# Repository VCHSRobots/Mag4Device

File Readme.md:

# Mag4 Project -- 4 Way Interface for SRX-MAG Encoders

## Background

The SRX Mag Encoder developed by Cross the Road Electronics (CTRE) has
been a mainstay for FRC Robots for many years.  It provides the ability
to read the angular postion of a shaft and provides two signals: a PWM
signal for abolute angle measurements and a quadrature signal for relative
measurements.  The electrical interface to the device is a socket for
small 10-pin ribbon cable that carries power and signals.  This ribbon
cable is usually connected to a Talon SRX motor controller that has a
mating socket.  Once connected to the Talon, the encoded information can
be read at the RoboRio by way of the CAN bus.  However, CTRE makes other
compatable accessories for this 10-pin cable so that the signals and be
broken out for other interfaces. 

As of 2023, an SRX Mag Encoder costs about $40.00.

Around 2018, CTRE and Vex Robots introduced the Falon Motor which has
a motor control and encoder built in.  That is, a Falcon does not need a Talon.
Without Talons, a SRX Mag Encoder does not have a natural interface device.
To alevate this problem CTRE also introduced a "CANCoder" which is an upgrade
to the SRX Mag Encoder.  The CANCoder has the same features as the SRX Mag
Encoder, except that the 10-pin socket has been replaced by CAN wiring.  

As of 2023, a fully decked out CANCoder costs about $80.00.  

## The Problem to be Solved

To build a swerve dirve robot with 4 wheels, 4 shaft encoders are necessary
to sense the direction of the drive wheels.  The built-in encoders in the Falcons
are not really suitable for this job since they do not report absolute 
angles.

In the past, we have used 4 CANCoders connected to a CAN bus to sense the
angle on the wheels.  This works, but with upwards of 30 devices on the CAN
bus -- the CAN bus begins to be over-utilised, leading to unwantted latency
of the resulting data (for all devices on the bus).  Also, 4 CANCoders cost
about twice as much as SRX Encoders.

Our idea is to use the cheaper SRX Encoders and thereby save money and reduce the
relience on the CAN bus.  Also, we may be able to significately reduce data latency.
Finally, we may be able to fuse the PWM signal with the Quadrature in the PICO 
to produce accurate angle measurments that are updated as fast as the quadrature
readings.  (Sadly, as of this writing, this has not been accomplished with the
required robustness for compentition.)

## Introducing the Mag4 Interface Device

We created a device, picture below, that has four 10-pin sockets to connect to
4 SRX Mag Encoders, and also a SPI port to connect to the RoboRio.  The device
is powered by 12 volts from the robot's Power Distribution Panel. 

The heart of the device is a Raspberry PICO board.  Software for the PICO and the
RoboRio is provided for an end-to-end solution of reading angular data from 4
devices at once and using the data in the RoboRio.  

This respository contains all facets of this project: Software for the PICO, Software
for the RoboRio, schematics and fabrication documents for the circuit board, as well as,
the documentation produced.

In addition, a sophicated test setup was built with a stepping motor that could
accurately rotate a shaft to known positions.  Data for this test station is also 
included in this respository.

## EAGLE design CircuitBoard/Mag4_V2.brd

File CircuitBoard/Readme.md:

# Mag4 Circuit Board

This respository contains all the Eagle Files necessary to produce
the PCB for the Mag4 Interface.  

Bill of Materials:
    
    1x PCB                      -- From AllPCB 
    1x Raspberry Pi PICO Board  -- From Amazon
    4x 10-Pin Socket            -- DigiKey, 1175-2649-1 
    1x LED, 1206                -- DigiKey, 732-4989-1
    1x VReg 5V 1.5A, DPAK       -- DigiKey, 497-7255
    1x 330 ohm Res, 1206        -- DigiKey, RMCF 1206FT330RCT
    2x Cap Tant, 1 UF, 1206     -- DigiKey, 478-2363
    1x JST male Socket, 2 Pin   -- From Amazon
    1x JST male Socket, 3 Pin   -- From Amazon
    1x JST male Socket, 5 Pin   -- From Amazon
    1x 3-Pin Header, 0.1 Pitch  -- From Amazon

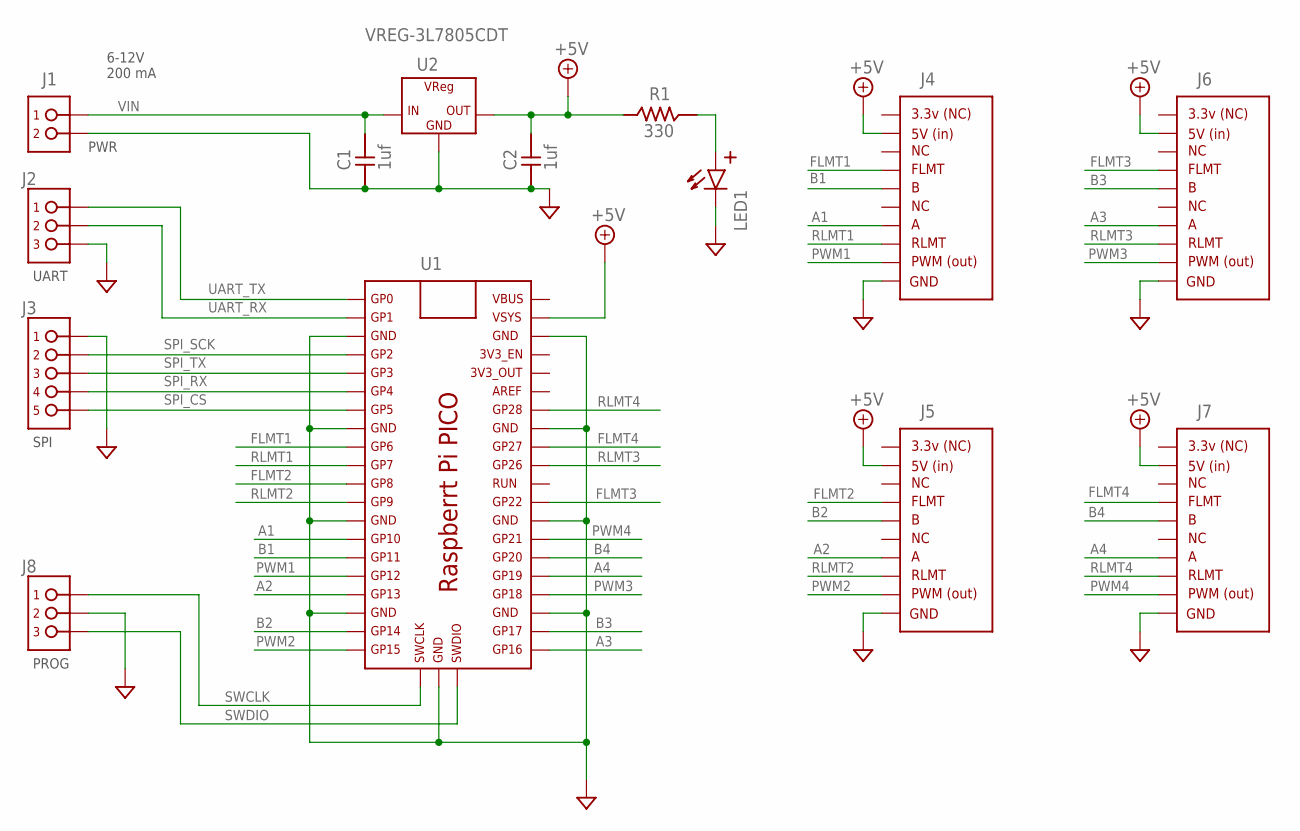
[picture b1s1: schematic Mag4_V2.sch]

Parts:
C1, C2: 1uf; C0805
J1: PINHDR_1X2-JST; JST-XH_098_VERT_1X2
J2: PINHDR_1X3XH-JST; JST-XH_098_VERT_1X3
J3: PINHDR_1X5-JST; JST-XH_098_VERT_1X5
J4, J5, J6, J7: MAG_ENCODER_CON; PINHDR_SMD_050_5X2
J8: PINHDR_1X3-100; PINHDR_TH_100_1X3
LED1: LED1206; LED_1206
R1: 330; R1206
U1: RASPBERRY_PI_PICOSMD; RASP_PI_PICO_SMD
U2: VREG-3L7805CDT; TO252-3

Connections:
+5V: C2.2, J4.2, J5.2, J6.2, J7.2, R1.P$1 (1), U1.P$39 (VSYS), U2.3 (OUT)
A1: J4.7, U1.P$14 (GP10)
A2: J5.7, U1.P$17 (GP13)
A3: J6.7, U1.P$21 (GP16)
A4: J7.7, U1.P$25 (GP19)
B1: J4.5, U1.P$15 (GP11)
B2: J5.5, U1.P$19 (GP14)
B3: J6.5, U1.P$22 (GP17)
B4: J7.5, U1.P$26 (GP20)
FLMT1: J4.4, U1.P$9 (GP6)
FLMT2: J5.4, U1.P$11 (GP8)
FLMT3: J6.4, U1.P$29 (GP22)
FLMT4: J7.4, U1.P$32 (GP27)
GND: C1.1, C2.1, J1.2, J2.1 (3), J3.1, J4.10, J5.10, J6.10, J7.10, J8.2, LED1.CATHODE(-) (CATHODE), U1.P$3 (GND1), U1.P$8 (GND2), U1.P$13 (GND3), U1.P$18 (GND4), U1.P$23 (GND5), U1.P$28 (GND6), U1.P$33 (GND7), U1.P$38 (GND8), U1.P$42 (GND_DEBUG), U2.FIN (GND)
unnamed: LED1.ANODE(+) (ANODE), R1.P$2 (2)
PWM1: J4.9, U1.P$16 (GP12)
PWM2: J5.9, U1.P$20 (GP15)
PWM3: J6.9, U1.P$24 (GP18)
PWM4: J7.9, U1.P$27 (GP21)
RLMT1: J4.8, U1.P$10 (GP7)
RLMT2: J5.8, U1.P$12 (GP9)
RLMT3: J6.8, U1.P$31 (GP26)
RLMT4: J7.8, U1.P$34 (GP28)
SPI_CS: J3.5, U1.P$7 (GP5)
SPI_RX: J3.4, U1.P$6 (GP4)
SPI_SCK: J3.2, U1.P$4 (GP2)
SPI_TX: J3.3, U1.P$5 (GP3)
SWCLK: J8.1, U1.P$41 (SWCLK)
SWDIO: J8.3, U1.P$43 (SWDIO)
UART_RX: J2.2, U1.P$2 (GP1)
UART_TX: J2.3 (1), U1.P$1 (GP0)
VIN: C1.2, J1.1, U2.1 (IN)

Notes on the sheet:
PWR
UART
SPI
6-12V 200 mA
PROG

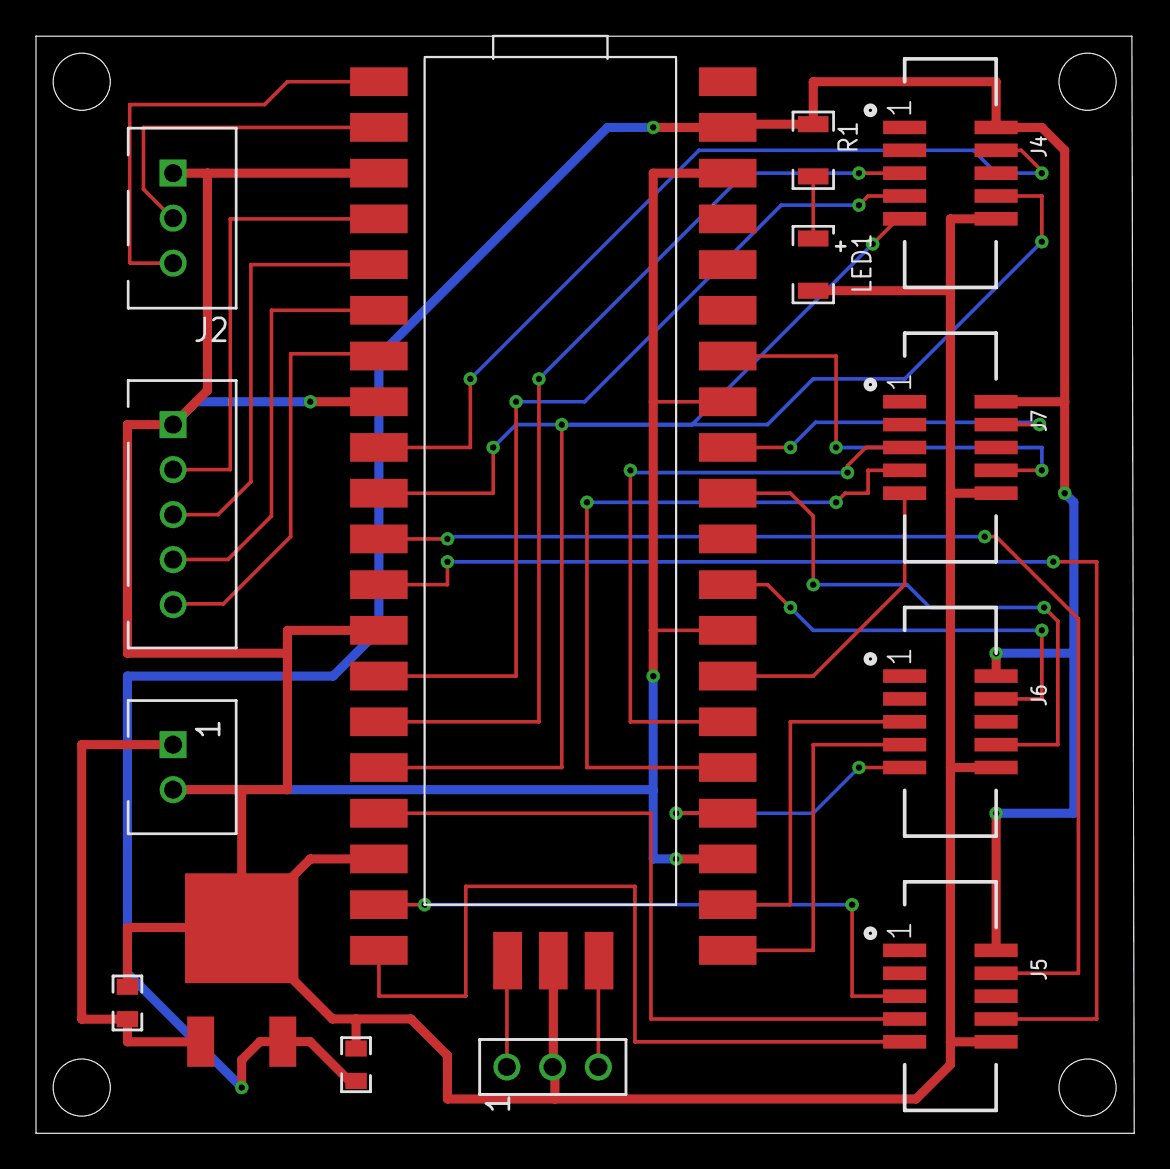
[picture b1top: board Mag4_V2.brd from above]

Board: 2 copper layers, 61.0 x 61.0 mm, 14 parts (0 on the bottom side), 32 nets.

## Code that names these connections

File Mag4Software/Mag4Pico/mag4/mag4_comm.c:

// mag4_comm.cpp -- Communication for the Mag4 interface device.

#include <stdio.h>
#include <string.h>
#include "pico/stdlib.h"
#include "pico/time.h"
#include "mag4.h"

#include "pico/binary_info.h"
#include "hardware/spi.h"
#include "pico/multicore.h"
#include "pico/binary_info.h"

// Data Protocol:
//
// The Mag4 interface device acts as a SPI slave -- it only responds to
// requests from the master SPI.
//
// Each transfer is two-way, i.e., the content of two buffers are exchanged,
// one being the input, the other output.  The buffers are the same size, and
// always 30 bytes long.
//
// Upon Chip Select (CS) being asserted, the most up-to-date info is loaded
// into the output buffer before the transfer.  Therefore, it is best to cycle CS
// for each transfer instead of holding it always asserted.  However, after each
// transfer, the buffer is reloaded in case CS is not being cycled.  That is,
// if CS is not being cycled, stale data might result.
//
// Each Transfer: 30 Bytes or 240 bits
// At 1MBit/sec = 0.24 msec delay per transfer, or a max update rate of over 4 KHz.
//
// Each Transfer follows this pattern:
//   Label:   v C1 C2 C3 C4 A1 A2 A3 A4 E1 E2 E3 E4  L
//   Bytes:   1  4  4  4  4  2  2  2  2  1  1  1  1  1  = 30 bytes / transfer
// 
// Where v is one byte that gives the version number indicator (currently = 5), 
// C1, C2, C3, C4 are the count ticks for ports 1-4 respectively,
// A1, A2, A3, A4 are the angles for ports 1-4 respectively,
// E1, E2, E3, E4 are the error in the angles for ports 1-4 respectively,
// L is one byte that contains the conditions of the limit switch inputs.  
//
// Counts are int32_t.  
// Angles are uint16_t, scaled so that there are 65536 ticks in the absolute circle.
// Error are uint8_t, scaled so that there are 256 ticks in the absolute circle.
//
// The Limit Switch byte is coded as one bit per switch, with this pattern: "44332211",
// where the pair of digits stand for the port number the bits are associated with.
// The first bit in each pair is for the forward limit direction, labeled "FLMT" on the
// SR-MAG encoder, and the second bit in each pair is for the reverse direction, 
// labeled "RLMT" on the SR-MAG encoder.

// See the schematic for these:

#define PIN_SPI_CLK    2  
#define PIN_SPI_MOSI   3
#define PIN_SPI_MISO   4
#define PIN_SPI_CS     5
#define PIN_FLMT1      6
#define PIN_RLMT1      7
#define PIN_FLMT2      8
#define PIN_RLMT2      9
#define PIN_FLMT3     22
#define PIN_RLMT3     26
#define PIN_FLMT4     27
#define PIN_RLMT4     28

#define CURRENT_VERSION 5
#define BUF_LEN 30

uint8_t limit_pins[] = {PIN_FLMT4, PIN_RLMT4, PIN_FLMT3, PIN_RLMT3, PIN_FLMT2, PIN_RLMT2, PIN_FLMT1, PIN_RLMT1};

uint8_t buf_out0[BUF_LEN];
 uint8_t buf_out1[BUF_LEN];
uint8_t *buf_out = NULL;
volatile bool start_transfer = false;
volatile bool can_switch = false;
volatile bool buf_lock = false;
volatile int bestbuf = 0;            // Latest buffer to use (either 0 or 1)
volatile long intr_cntr = 0;

uint8_t buf_in[BUF_LEN];
uint32_t io_cycles = 0;
uint32_t buf_switches = 0;

// Setup the SPI.  It took lots of debugging on the ossilliscope to get
// the SPI setup to work with the RoboRio.
void setup_spi_output() {
    spi_init(spi0, 1000 * 1000);
    spi_set_format(spi0, 8, SPI_CPOL_1, SPI_CPHA_1, SPI_MSB_FIRST);  // Must be THIS WAY!  
    spi_set_slave(spi0, true);
    gpio_set_function(PIN_SPI_MISO, GPIO_FUNC_SPI);
    gpio_set_function(PIN_SPI_CLK, GPIO_FUNC_SPI);
    gpio_set_function(PIN_SPI_MOSI, GPIO_FUNC_SPI);
    gpio_set_function(PIN_SPI_CS, GPIO_FUNC_SPI);
}

// Setup the pins for the limit switches.  Note that some pins (the ADCs) must
// be set to SIO and input enabled.  For other pins, that is the default.
void setup_limit_inputs() {
    for(int i = 0; i < 8; i++) {
        gpio_set_function(limit_pins[i], GPIO_FUNC_SIO);
        gpio_set_input_enabled(limit_pins[i], true);
        gpio_set_dir(limit_pins[i], GPIO_IN);
        gpio_pull_up(limit_pins[i]);  // Not sure this is necessary
    }
}

// Retrives the condition of all the limit switch inputs, and builds a byte.
uint8_t get_limit_switch_byte() {
    int lims = 0;
    for(int i = 0; i < 8; i++) {
        int v = 0;
        if (gpio_get(limit_pins[i])) v = 1;
        lims = (lims << 1) | (0x0001 & v);
    }
    return lims;
}

// For Debugging Purposes
char* buftostr(uint8_t buf[]) {
    static char line[100];
    char temp[20];
    line[0] = 0;
    for(int i = 0; i < BUF_LEN; i++) {
        sprintf(temp, "%2x ", buf[i]);
        strcat(line, temp);
    }
    return line;
}

// Gets info from the background processes and encodes it for output.
void load_buffer(uint8_t *buf) {
    int32_t quad_counts[4];
    uint8_t buferr[4];
    int indx = 0;
    buf[indx++] = CURRENT_VERSION;
    quad_get_all_counts(quad_counts);
    memcpy(buf + indx, quad_counts, 16);
    indx += 16;
    for(int iport = 0; iport < 4; iport++) {
        float angle;
        uint8_t ierr = 0;
        uint16_t iangle = 0;
        int okay = get_angle_raw(iport, &angle);
        if (okay == 0) {
            ierr = 255;
            iangle = 0;
        }
        else {
            uint32_t iiangle = (uint32_t) (angle * 65536.0);
            if(iiangle > 65535) iiangle = 0;  
            iangle = (uint16_t) iiangle;
            float angle_err = get_angle_error(iport);
            uint32_t iierr = (uint32_t) angle_err * 256.0;
            if (iierr > 255) iierr = 255;
            ierr = (uint8_t) iierr;
        }
        memcpy(buf + indx, &iangle, 2);
        indx += 2;
        buferr[iport] = ierr;
    }
    // Append the error data -- four bytes...
    for (int iport = 0; iport < 4; iport++) {
        buf[indx++] = buferr[iport];
    }
    buf[indx++] = get_limit_switch_byte();
}

// On interrupt, a transfer is about to take place -- measured to be 7us in
// the future for first bit.  Here, we quickly switch buffers, then set the go flag.
void cs_iqr_handler(uint gpio, uint32_t event_mask)
{
    if(event_mask & GPIO_IRQ_EDGE_FALL) {
        if (gpio == PIN_SPI_CS) {
            intr_cntr++;
            while(buf_lock) ;  // wait till okay to change pointers.
            if (bestbuf == 0) buf_out = buf_out0;
            else              buf_out = buf_out1;
            can_switch = false;
            start_transfer = true;
        }
    }
}

// Processor 1 is responsible for monitoring the SPI bus and responding
// to data requests.
void proc1() {
    setup_spi_output();
    setup_limit_inputs();
    // Set up an interrupt on CS line 
    gpio_set_irq_enabled_with_callback(PIN_SPI_CS, GPIO_IRQ_EDGE_FALL, true, cs_iqr_handler);
    gpio_set_irq_enabled(PIN_SPI_CS, GPIO_IRQ_EDGE_FALL, true);
    while(1) {
        while(!start_transfer) ;  // Wait for single to go.
        spi_write_read_blocking(spi0, buf_out, buf_in, BUF_LEN);
        //char *p = buftostr(buf_out);
        //printf("buf_out = %s\n", p);
        start_transfer = false;
        can_switch = true;
        io_cycles++;
    }
}


// Processor 0 is responsible for reading the encoders.  Note that
// all the hard work is done via interrupts in the background.  The
// main loop is only needed to keep the output buffer loaded with
// the most up-to-date info. Note also, that processor 1 is started
// by processor 0.
int main()
{
    int32_t quad_counts[4];

    stdio_init_all();
    setup_spi_output();
    printf("Mag4 PWM/Quadrature Interface Device\n");
    init_mag4();
    multicore_launch_core1(proc1);

    // Info about this loop:  Cycle time is about 59 usec.  Used with the RoboRio, a transfer
    // occurs once every 20 milliseconds, and lasts .3ms. Therefore the duty cycle is 0.015.
    // When transefers are not occuring, the buffers are being updated and switched.  Our
    // debug counts show the the ratio of switched to non-switched is 0.009.  Therefore,
    // switching is occurring very often -- leading one to believe that the max latency
    // through the system is 59 usecs for the buffer load, and then .3 msecs for the transfer.
    // Therefore the latency at the RoboRio should only be about .36 msec!
    while (true)
    {
        if (bestbuf == 0) {
            load_buffer(buf_out1);
        } else {
            load_buffer(buf_out0);
        }
        if (can_switch) {
            buf_lock = true;
            bestbuf++;
            if(bestbuf > 1) bestbuf = 0;
            buf_lock = false;
        }
    }
}

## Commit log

2023-07-10 Initial Commit
    Initial Commit After 6 months of work, and mostly finished
2023-07-10 Initial Stuff
2023-07-10 Updating Readme
2023-07-10 Adding Circuit Board Files
2023-07-10 Adding Docs and Circuit Stuff
2023-07-10 More On TestBoard
2023-07-10 More Doc Changes
2023-07-11 More Documentation
2023-07-11 Keep Production uf2 in github
